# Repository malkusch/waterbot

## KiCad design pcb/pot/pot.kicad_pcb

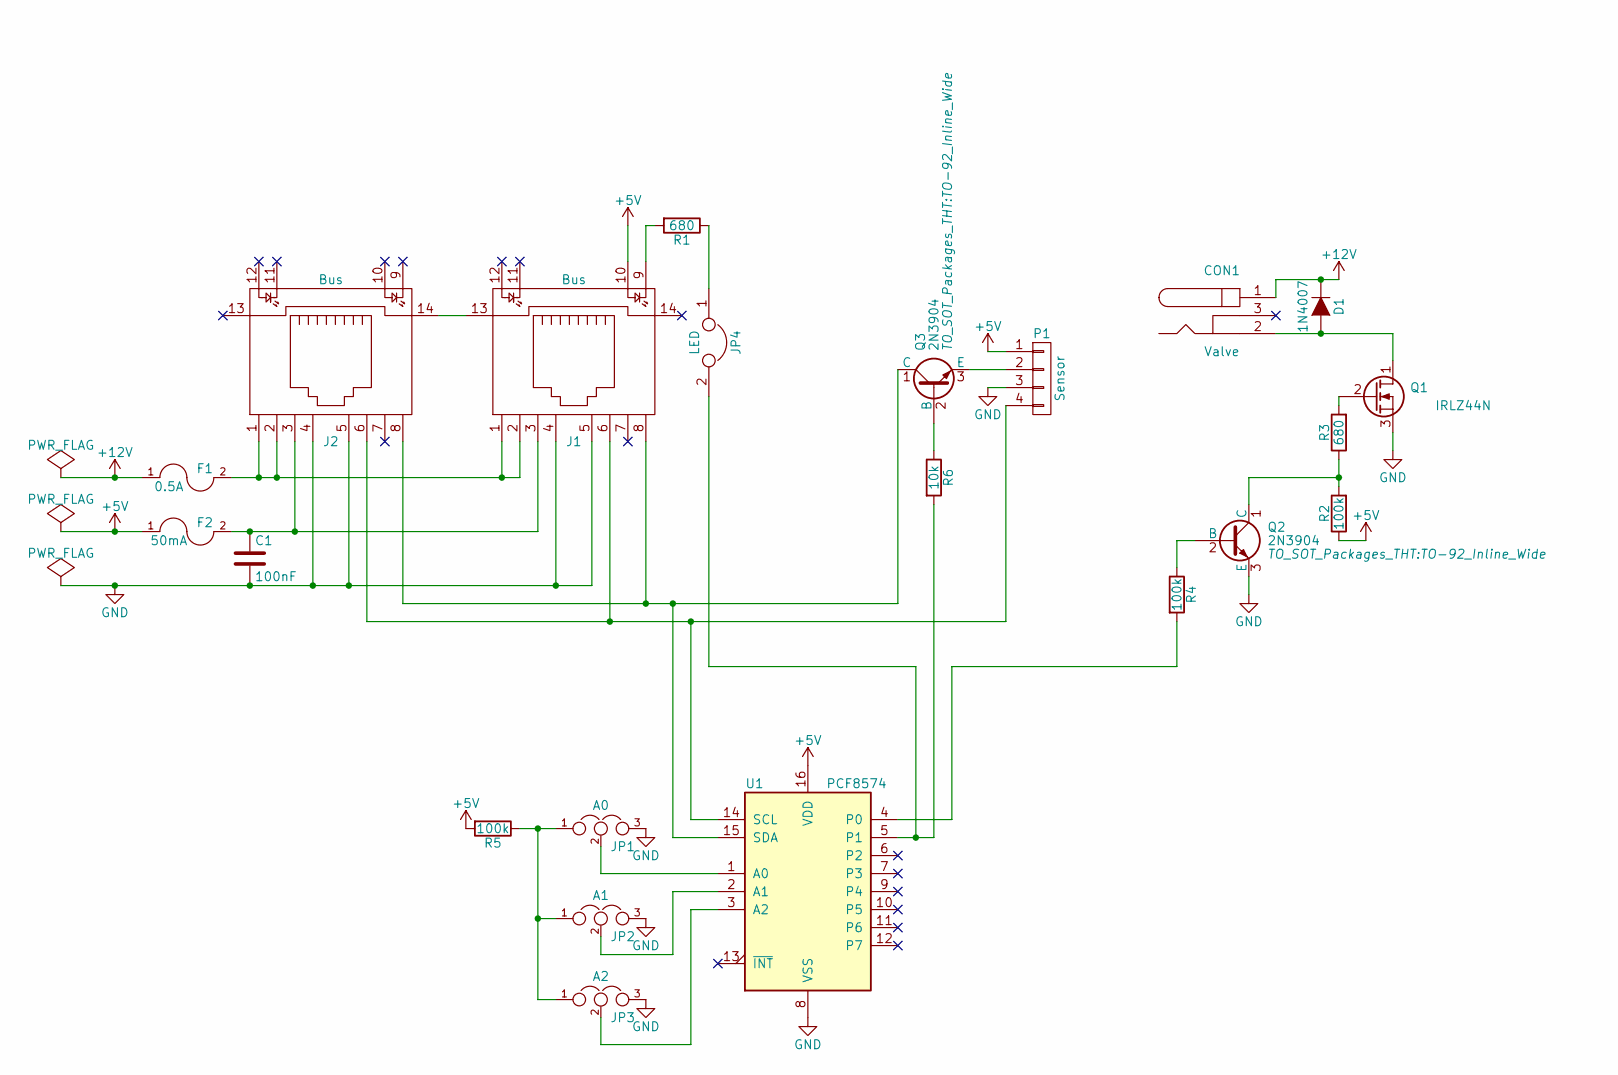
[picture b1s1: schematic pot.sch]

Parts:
C1: 100nF; C_Disc_D4.3mm_W1.9mm_P5.00mm
CON1: Valve; BARREL_JACK
D1: 1N4007; D_A-405_P7.62mm_Horizontal
F1: 0.5A; Fuse_TE5_Littlefuse-395Series
F2: 50mA; Fuse_TE5_Littlefuse-395Series
J1, J2: Bus; RJHSE538X
JP1: A0; Pin_Header_Straight_1x03_Pitch2.54mm
JP2: A1; Pin_Header_Straight_1x03_Pitch2.54mm
JP3: A2; Pin_Header_Straight_1x03_Pitch2.54mm
JP4: LED; Pin_Header_Straight_2x01_Pitch2.54mm
P1: Sensor; JST_XH_S04B-XH-A_04x2.50mm_Angled
Q1: IRLZ44N; TO-220_Vertical
Q2, Q3: 2N3904; TO-92_Inline_Wide
R1, R3: 680; R_Box_L13.0mm_W4.0mm_P9.00mm
R2, R4, R5: 100k; R_Box_L13.0mm_W4.0mm_P9.00mm
R6: 10k; R_Box_L13.0mm_W4.0mm_P9.00mm
U1: PCF8574; DIP-16_W7.62mm

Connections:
+5V: F2.1, J1.10, P1.1, R2.1, R5.2, U1.16 (VDD)
+12V: CON1.1, D1.1 (K), F1.1
GND: C1.2, J1.4, J1.5, J2.4, J2.5, JP1.3, JP2.3, JP3.3, P1.3, Q1.3 (S), Q2.3 (E), U1.8 (VSS)
unnamed: C1.1, F2.2, J1.3, J2.3
unnamed: CON1.2, D1.2 (A), Q1.1 (D)
unnamed: F1.2, J1.1, J1.2, J2.1, J2.2
unnamed: J1.6, J2.6, P1.4, U1.14 (SCL)
unnamed: J1.8, J2.8, Q3.1 (C), U1.15 (SDA)
unnamed: J1.9, R1.2
unnamed: J1.13, J2.14
unnamed: JP1.1, JP2.1, JP3.1, R5.1
unnamed: JP1.2, U1.1 (A0)
unnamed: JP2.2, U1.2 (A1)
unnamed: JP3.2, U1.3 (A2)
unnamed: JP4.1, R1.1
unnamed: JP4.2, R6.2, U1.5 (P1)
unnamed: P1.2, Q3.3 (E)
unnamed: Q1.2 (G), R3.2
unnamed: Q2.1 (C), R2.2, R3.1
unnamed: Q2.2 (B), R4.1
unnamed: Q3.2 (B), R6.1
unnamed: R4.2, U1.4 (P0)

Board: 2 copper layers, 22 parts (0 on the bottom side), 22 nets, no tracks yet.

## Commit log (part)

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2017-05-14 Implement automatic watering bot
2017-05-17 Make it run on the Arduino
2017-05-17 Decrease probe frequency
2017-05-17 Make this project buildable in the Arduino Eclipse IDE
2017-05-17 Analyze moisture sensor data
2017-05-18 Fix int overflow
    maxPumplessDays was overflowing on the way to become milliseconds.
2017-05-18 Pause before the first sensor readings
    When reading the sensor instantly, it reads a too low voltage. This
    commit ads a pause of a few seconds before the first sensor read.
2017-05-19 Plot hours in data analysis
2017-05-19 Support multiple pots
    Each pot has its own sensors and a valve. If a pot decides it's time for
    watering, it opens its valve and starts the pump. When finished the pump
    is stoped and the valve closed.
    Pots are checked sequentially. This makes the code easier and prevents
    drawing too much current at once.
2017-05-19 Refactor project to have more structure
    Ok, this commit does a few things:
    - Separate the model from infrastructure code
    - Refactor the Logger into an abstract Logger and a SerialLogger
    implementation. As soon as my Data Logging Shield arrives, I will
    implement a SDCard logger.
    - Refactor Valve into an interface and OnboardValve. I'm planing to
2017-05-20 Wait a short time for valves and the pump
    Valves and the pump don't act instantly. This commit adds a delay after
    opening and closing valves and turning off a pump. This should
    effectively avoid pumping against a completely closed system.
    Before this commit a the pump would be activated right after setting the
    valve pin to HIGH. This effectivly turns on the pump and the valve in
    the same moment, Until the valve did not physically open, the pump would
2017-05-20 Add 2 more pots
2017-05-20 Fix new multi pot code
2017-05-20 Log free memory
2017-05-20 Monitor sensor health
    Sensors could be wired up wrongly or simply break. This commit checks
    that the standard error is small and also the readings are not at the
    extreme ends (e.g. unpluged sensor). Also the mean was replaced with the
    median as noise reduction. The median is more resistant against
    outliners.
2017-05-21 Format log level to string without default case
    Without a default case the compiler would issue a warning if an enum
    member was forgotten.
2017-05-21 Analyze data of multiple pots
2017-05-21 Combine multiple data sets in analyzation
2017-05-21 Reduce memory usage
    The pots now share a pointer to the pump. Before the pump was copied in
    each pot.
2017-05-21 Add Pot::water(seconds)
2017-05-21 Refactor Pot::waterIfNeeded() into AutomaticWaterService
2017-05-21 Water all pots on boot up
2017-05-21 Add DryStrategy
2017-05-22 Consider millis() overflow
2017-05-22 Log watering
2017-05-22 Make it testable, but this is WiP
2017-05-23 Analyze 24 average
    Temperature has a high effect on resistance. You can see a 24h
    oscilation in the data. I'd like learn if the 24h average is a better
    feature to learn about dryness.
2017-05-23 Rename project
    This project is only about watering plants.
2017-05-23 Integrate CI
2017-05-24 Pause between readings
    It turns out that the wires save some energy (capacitive and/or
    inductive). This pause should help to remove that saved energy to
    Ground. Otherwise it would affect the sensor readings. I.e. the first
    reading of a bulk would be very different as subsequent, as it doesn't
    have the saved energy in the wires.
2017-05-24 Debug sensors during pause
    Arduino resets itself during pausing. I assume there's a voltage spike
    in those long wires.
2017-05-24 Save energy
2017-05-24 Analyze more logs
2017-05-24 Pause between switching polarisation
    An instant polarisation change might have inductive and capacitive
    effects on the first readings after the switch. This commit divides
    reading from a sensor in two batches which have a pause of no voltage in
    between.
2017-05-25 Invert moisture value
    After the last refactoring of OnboardMoistureSensor, I accidentially
    inverted the values of the moisture sensor.
2017-05-25 Log reset reason
2017-05-25 Test millis() overflow
2017-05-26 Align X axises
2017-05-27 Integrate temperature sensor
2017-05-30 Fix bug in data parsing
2017-05-30 Use RTC
    This commit adds support to the DS1307 RTC. The logger would now use the
    unix timestamp as first value. When the RTC is not running (e.g. battery
    was empty), it will set the compilation time.
2017-05-30 Log to SD card
    Logging to the SD shield requires 4 pins (SPI). That's why one pot was
    removed with this commit. Also all other pots got a different wiring.
    More pots will be supported with mulitplexing or a BUS (1-wire or I²C).
2017-05-31 Support removing and inserting of SD card
2017-05-31 Implement DC moisture sensor
2017-06-01 Increase moisture read delay
    After some tests on the breadboard it turns out, that the sensor needs
    at least 8 seconds to deliver a stable voltage.
2017-06-01 Set logger implementation as configuration
2017-06-01 Introduce namespaces
    This is just a very small refactoring to get familiar with C++'s
    namespaces. I will refactor other classes over time.
2017-06-02 Add pin abstraction
    I don't add this additional abstraction for fun. It's necessary to
    support everything on multiplexed pins as well.
2017-06-02 Support CD74HC4067 multiplexer
2017-06-02 Support digital output pins with PCF8574
    The PCF8574 adds further digital IO pins via I²C.
2017-06-06 Analyze new log format
2017-06-16 Analyze more sensor data
2017-06-16 Design water control breadboard
2017-06-17 Fix inverted pump behaviour
2017-06-17 Use timer strategy for watering
    The current sensors depend too much on temperature and I don't have a
    temperature sensor yet. For a first working prototype I will simply
    water the pots once a day.
2017-06-24 Add PotRepository
2017-06-24 Add AutomaticWaterApplicationService
2017-06-25 Implement Pots on the I²C bus
2017-06-25 Add LED for each pot
2017-06-26 Decrease power consumption
2017-06-28 Fix broken millis()
    When entering a power save mode, millis() stops working. This commit
    changes the behaviour into just entering idle mode.
2017-06-28 Support AM2321 sensor
    The AM2321 humidity and temperature sensor uses one I²C address. I have
    to multiplex between other sensors. The original idea, was simply
    controlling the power of the sensor with the IO expander. While testing
    that, it doesn't work reliably.
    First, althout the sensor uses way less
    than 4mA, I could't source the voltage from the expander, so I had to
2017-06-30 Support more pots
    This commit refactors the code to safe some SRAM. This allows 15 pots
    with the SerialLogger. When using the SDLogger, significantly less pots
    are supported. If you need to support more than 15 pots, you can
    implement a NullLogger. This will free up some memory for more pots.
    Note, with the PCF8574 there are only up to 16 pots on I²C supported.
    However you could add even more pots directly on the Arduino's I/O pin
2017-06-30 Add pot PCB
2017-06-30 Redefine moisture as a float between 0 and 1
2017-07-03 Water all pots automatically
    This commit adds a DryStrategyFactory, so that the PCF8574PotRepository
    can build a DryStrategy for each pot. Previously the DryStrategy was
    shared between pots, which leads to watering only the first pot.
2017-07-04 Retry on failed AM2321 read
2017-07-04 Place pot LED on sensor pin
    The sensor pin is most of the times LOW, so it could sink the LED's
    current. When reading the sensor the LED will turn off. This will also
    help as indicator to see if the pin was successfully restored to LOW
    after reading the sensor. Currently the PCF8574 lib doesn't pass any
    error codes further. If an LED is off, it's a good indicator for an
    invalid state.
2017-07-04 Fix bus switch
2017-07-04 Log sensor uid
    This should help to confirm that for each pot a different sensor is
    used.
2017-07-04 Retry on pin PCF8574 I²C failures
2017-07-19 Increase watering frequency
    My pots are pretty dry.
2017-07-20 Fix bus switch
    During prototyping I destroyed a bunch of N7000. It seems they're very
    sensitive and need a pull down on the Gate. During prototyping I
    connected the gate directly to GND or VDD. I don't know if the act of
    unplugging the gate manually did destroy them or connecting them
    directly. Adding a pull down resistor fixed that issue. However it might
    not be necessary when using the port extender. I need to investigate
2017-07-21 Decrease watering frequency
    Three times a day is too much. One was too less. I try three now.
2017-08-02 Revert "Log sensor uid"
    It turns out, that reading the id on an AM2322 doesn't work. Moreover it
    prevents reading any other data from the sensor.
    This reverts commit be4ef404995391e0da384abbd37b7a7dfca84cf0.
2017-08-02 Add BME280Sensor
2017-08-02 Detect sensor automatically
    When using the PCF8574 port extender as bus switch, any switched I²C
    sensor (currently AM2321, AM2322 and BME280) will be used automatically.
2017-08-05 Fix wrong humidity in BME280
2017-08-05 Ignore PCF8574 with same address as BME280
    The BME280 uses the address B1110110 which can also be used by a port
    expander. The BME280 might become unsupported as it is very expensive.
    But for now, while still beeing in evaluation, port expanders with that
    address are not supported.
2017-08-05 Get faster responses in DEV profile
2017-08-05 Show detected and setup pots (again)
    This commit adds the pot LED back again. It turns out, it is really
    helpful to see which pots are detected and setup successfully.
2017-08-05 Add HTU21D sensor
    That's an extremly cheap humidity and temperature sensor. A break out
    board costs less than 2$. Note: it's a 3.3V device and therefore needs a
    logic level shifter for the I²C bus.
2018-06-09 Use a MOSFET as bus switch
2018-06-09 Update dependencies
2018-06-09 Wait longer to recover from failed sensor
2018-06-09 Pull up bus switch per default
    The IO expander is up per default and up means that the bus is switched
    off (hence a P-channel transistor).
2018-06-11 Signal where sensors were found
    This commit does a few things. First, it assumes each bus switch is off
    per default. That makes the logic in software simpler. Then the signal
    LED on each expander is used to signal where a sensor was detected. This
    helps to see if the system detected everything successfully.
2018-06-12 Revert to HTU21DF upstream
    Upstream did fix the issue in their repository. My fix is no more
    needed.
2018-06-25 Update libraries
2018-06-28 Ignore errors from sensors
2018-06-28 Generalize probed and switched sensors
    It turns out that I can't use a humidity sensor to just measure moisture
    in the soil. Humidity in soil is always 100%. However in a recent
    experiment I measure humidity near soil. Currently it is additionally
    30% more humid than air. If this turns out to be feasible, I will need a
    reference sensor for the current air humidity. The reference sensor
    would be globally accessible on the I2C bus and can be switched directly
2018-06-28 Decrease memory consumption
    Using pointers when there is only one existing reference does increase
    the memory footprint. This commit does refactor such usages to values.
2018-06-28 Blink LEDs on pots
    During the pause, the LEDs of a pot do blink. This helps to signal that
    the firmware is still running. Also this commit adds the concept of an
    LED to the Pot object. I might in a follow up commit use that to signal
    that something was wrong with a specific pot (e.g. a sensor reading
    failed).
